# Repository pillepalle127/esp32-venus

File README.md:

# ESP32-S3 statt Venus OS

Ich will die Funktionen von Venus OS, die ich nutze, auf einem ESP32-S3 nachbauen. Eine Portierung geht nicht: Venus OS ist eine Linux-Distribution, und ein kompletter Build braucht private Repos von Victron.

## Ziel

1. Den Pi ersetzen (`raspberrypi2`, 192.168.1.10).
2. Den Netzzähler gleich mit übernehmen (MT681, heute `victron_meter.be` auf Tasm_Kellercenter2). Später ziehen auch Lüfter und BME280 um, dann entfällt der Tasmota ganz.
3. Zum Schluss die zwei ESP32-S3 ersetzen, die heute parallel laufen: die OpenDTU-OnBattery (DTUoB_WP) regelt den WP-HMS, die OpenDTU (HMS Garage) liefert nur Werte. Die Wechselrichter bleiben.

## Anlage laut Venus (02.11.2026)

| Dienst | Instanz | Gerät | Anschluss |
|---|---|---|---|
| `vebus.ttyUSB0` | 288 | MultiPlus-II 48/5000/70-50 | VE.Bus |
| `solarcharger.ttyUSB1` | 293 | BlueSolar MPPT 100/20 48V | USB |
| `solarcharger.ttyUSB2` | 294 | BlueSolar MPPT 100/20 48V | USB |
| `solarcharger.ttyUSB4` | 296 | BlueSolar MPPT 100/20 48V | USB |
| `solarcharger.ttyUSB5` | 291 | SmartSolar MPPT 100/20 48V | USB |
| `solarcharger.ttyUSB6` | 288 | SmartSolar MPPT 100/20 48V | USB |
| `solarcharger.ttyUSB7` | 292 | BlueSolar MPPT 100/20 48V | USB |
| `battery.ttyUSB8` | 291 | SmartShunt IP65 300A | USB |
| `battery.socketcan_can1` | 512 | JK-BMS | CAN |
| `grid.ve_TM974E88` | 40 | Netzzähler MT681 | SML 9600 Baud an Tasm_Kellercenter2. Venus liest per Modbus UDP von 192.168.1.33, `victron_meter.be` gibt den Tasmota als Victron-Zähler VM-3P75CT aus |
| `pvinverter.http_34`, `inverter.http_34` | 34 | Hoymiles HMS-1600 (Garage) und HMS-2000 (WP) | Funk über OpenDTU und OpenDTU-OnBattery, Venus liest per HTTP (`dbus-opendtu_Garage`, `dbus-opendtu_WP`) |
| `pvinverter.mqtt_pv_100` | 100 | Growatt MIC, über `dbus-mqtt-pv` | MQTT |

- Akku: zwei Packs parallel, je 15s1p aus Zellen Eve LF230, jedes Pack mit eigenem JK-BMS der PB-Reihe. Primär: JK-PB2A16S20P V19 (8–16S, 200 A, 2 A aktiver Balancer). Sekundär: JK-PB1A16S15P V15 (8–16S, 150 A, 1 A aktiver Balancer).
- Heizung: Das JK-BMS schaltet seinen Heizausgang selbst. Freigabe bei der PB-Reihe über RS485, Register `0x0114` Bit 0 (`HeatEN`, lesen und schreiben, im selben Register stehen weitere Schalter), dazu Start- und Stopptemperatur. Über CAN gibt es keinen Befehl dafür. Quelle: [jkbms-rs485-addon #177](https://github.com/jean-luc1203/jkbms-rs485-addon/issues/177), an meinen BMS nicht geprüft.
- Unter 0 °C an der Batterie muss der Heizer aktiviert werden. Der Heizer ist noch nicht aktiv, deshalb muss unter 0 °C das Laden abgeschaltet werden.
- Als SoC gilt immer der Wert des SmartShunt (battery 291). Der SoC des JK-BMS driftet viel stärker und hat einen hohen Messfehler.
- Die seriellen Anschlüsse laufen heute über 2 × FT4232 am Pi, alle Kanäle mit Isolatoren.
- Firmware der MPPT v1.74 (`372` = `0x174`), MultiPlus v508 (`1288` = `0x508`).
- `can1`: 500 kbit/s, MCP2515 am Pi.
- Die MPPT laufen nachts aus der Batterie und lassen sich lesen.

## Entscheidungen

- Ein ESP32-S3 für alles.
- Die FT4232 ersetze ich durch einen CH348. Der läuft allerdings nicht an Venus.
- Von OpenDTU-OnBattery nutze ich nur Überwachung und Steuerung des Hoymiles HMS zur Einspeisung. Es ist deshalb keine Basis für dieses Projekt.
- Die Verbindung zu VRM bleibt (Entscheidung vom 18.11.2026). ESP_venus meldet selbst an VRM, so wie der vrmlogger in Venus OS. Was Venus heute sendet: [docs/vrm.md](docs/vrm.md).

## Serielle Anschlüsse

- Der USB-Host des S3 kann nur Full Speed und hat 8 Kanäle, jeder Endpunkt belegt einen. 2 × FT4232 geht deshalb nicht, schon einer braucht 9.
- Der CH348 läuft am S3 mit Full Speed über 4 Bulk-Endpunkte, mit EP0 sind das 5 von 8 Kanälen. Sein Protokoll ist nicht offen. Die Befehle in meinem Treiber stammen aus `ch9344ser_linux` von WCH (GPL-2.0), verglichen mit dem ESPHome-PR #14586.
- Für die beiden RS485 zu den Packs nehme ich einen SC16IS752 (CJMCU-752, SPI, 2 UARTs). Der CH9434 ist schlecht verfügbar.
- Pegel: Die MPPT senden mit 5 V, die Isolatoren bleiben. Der CH348 läuft nur mit 3,3 V, die Isolatoren auf seiner Seite deshalb auch. 5 V vertragen nur RXD0, RXD2, RXD4 und RXD7.

## Belegung (wie verdrahtet, 14.11.2026)

| Funktion | Signal | GPIO | Anschluss |
|---|---|---|---|
| VE.Bus, UART1, 256000 Baud | RX / TX | 4 / 5 | RS485-Modul (MS2548), über ADuM1201 und B0505S isoliert |
| MT681 Haus, UART2, 9600 Baud | RX | 7 | Pfostenstecker MT681: GND, 3V3, Haus, WP |
| MT681 Wärmepumpe, RMT, 9600 Baud | RX | 6 | Pfostenstecker MT681 |
| Kellerlüftung, I²C | SDA / SCL | 16 / 15 | die beiden BME280 (0x76 außen, 0x77), je ein Pfostenstecker: GND, 3V3, SDA, SCL |
| Funk, ein CMT2300A für beide HMS | CSB, SDIO, SCLK, FCSB | 8, 3, 46, 9 | Modul per Pigtail am S3 angelötet, VCC an 3V3 |
| Kellerlüftung | Lüfter | 11 | Relais |
| Reserve | Relais 2 | 12 | Relais |
| JK-BMS, TWAI, 500 kbit/s | TX / RX | 14 / 13 | TJA1050, über ADuM1201 und B0505S isoliert |
| JK-BMS, RS485 je Pack, SC16IS752 per SPI | CS, SI, SO, SCLK | 2, 42, 41, 38 | CJMCU-752 mit Quarz 1,8432 MHz (höchstens 115200 Baud), VCC an 5 V für den AMS1117 auf dem Modul, UART A und B je über ADuM1201, B0505S und RS485-Modul (MS2548) isoliert, nur für die Zellspannungen |
| RGB-LED des Boards | WS2812 | 48 | über die Lötbrücke „RGB“ |
| Reserve | | 1, 10, 17, 18, 21, 39, 40, 47 | |
| Flashen, UART0 beim Start | TX / RX | 43 / 44 | COM-Buchse auf dem Board |
| CH348, USB-Host | D− / D+ | 19 / 20 | native USB-Buchse, 5 V über die Brücke `USB-OTG` |
| nicht beschalten | Strapping | 0, 45 | |
| belegt | Octal-PSRAM | 33–37 | |

| CH348 | Gerät |
|---|---|
| Port 0–5 | die 6 MPPT, über die vorhandenen Isolatoren |
| Port 6 | SmartShunt, über den vorhandenen Isolator |
| Port 7 | frei, für einen weiteren MPPT |

- Zum JK-BMS laufen zwei Wege. **CAN steuert:** Ladegrenzen, Alarme, SoC, beide Packs zusammengefasst, ohne CAN keine DVCC-Vorgaben. **RS485 zeigt an:** einzelne Zellspannungen, die Regelung hängt nicht daran.
- Der Netzzähler bleibt am eigenen UART, er liefert das Regelsignal fürs ESS. Der zweite MT681 läuft per RMT als Empfangs-UART. Die Zellspannungen beider Packs laufen über den SC16IS752, UART0 bleibt Konsole.
- Welcher MPPT an welchem Port hängt, spielt keine Rolle: Die Firmware erkennt jedes Gerät an seiner Seriennummer und gibt ihm die Instanz von heute.
- GPIO 3 und 46 sind Strapping-Pins und tragen nur Eingänge des CMT2300A. GPIO 46 hält der interne Pull-down beim Reset low. GPIO 3 wirkt nur mit gesetzter eFuse `STRAP_JTAG_SEL`.
- Ein Ausfall des WLAN trifft nur ioBroker und VRM, nicht die Regelung.

## Trennung und Transceiver

Lochraster-Plan: [docs/layout_lochraster.drawio](docs/layout_lochraster.drawio), Belegung der Stiftleisten: [docs/layout_lochraster.md](docs/layout_lochraster.md).

Eigene Platine, Plan mit Steckverbindungen und Blockdiagramm: [docs/platine.md](docs/platine.md).

- Die BMS schalten im Minus-Zweig. Hängt der S3 ohne Trennung an zwei Stellen, überbrückt seine Masse einen offenen BMS-Schalter. Ich trenne deshalb VE.Bus, CAN und RS485, jeweils an TX und RX, mit ADuM1201 und einem eigenen B0505S-1W je Busseite. GND bleibt am Bus.
- Das ist eine Funktionstrennung gegen rund 60 V, kein Schutz vor Netzspannung.
- Der B0505S-1WR3 ist ungeregelt und braucht mindestens 20 mA Last. Der TJA1050 sendet nur bei 4,75–5,25 V. Ist die Spannung bei wenig Last zu hoch, hilft ein Lastwiderstand (250 Ω = 10 % Last).
- Der ADuM1201AR reicht für CAN: höchstens rund 0,8 µs Laufzeit, der S3 tastet nach 1,6 µs ab.
- **RS485-Module (VE.Bus und Packs):** Auf den Modulen im Lochraster sitzt ein MS2548 von Ruimeng, kein MAX13487. Die eigene Platine nimmt das kleine Modul mit MAX13487 („RS485 V2.05“), siehe [docs/platine.md](docs/platine.md#busseiten).
- Der MS2548 schaltet die Richtung selbst: D low treibt low, D high treibt kurz high und gibt frei. Den Ruhezustand halten Pull-up an A und Pull-down an B.
- An VE.Bus müssen Pull-up und Pull-down runter. Mit ihnen lag der Bus bei 4,5–10 kΩ, der MultiPlus ging beim Einstecken auf Störung (17.11.2026). Ohne sie empfängt und sendet der MS2548 an VE.Bus: Sync, 0 Prüfsummenfehler, jeder ESS-Befehl quittiert.
- **TJA1050 (CAN):** Der TWAI des S3 braucht nur den Transceiver, keinen MCP2515.
- Eigene Platine: CAN an Stecker X5 (1 GND, 2 CANH, 3 CANL). Layout: [docs/platine.md](docs/platine.md#layout).

## Relaistreiber

Zwei 5-V-Relais von Finder, je Low-Side über AO3402 (100 Ω Gate, 10 kΩ Pull-down, Freilaufdiode). GPIO high schaltet ein. Der AO3402 hat laut Datenblatt höchstens 85 mΩ bei 2,5 V Gate-Spannung.

| Relais | GPIO | In der Firmware |
|---|---|---|
| Lüfter, Kellerlüftung | 11 | `FAN_RELAY` |
| Relais 2, Reserve | 12 | `RELAY2` |

- Eigene Platine: Stecker X6 (Lüfter) und X7 (Relais 2), je 1 +5V, 2 Schalter. Layout: [docs/platine.md](docs/platine.md#layout).
- Firmware: Nach dem Start bleiben GPIO 11 und 12 Eingang, erst ein Knopf auf der Seite macht sie zum Ausgang.

## DVCC

DVCC ist aktiv, der S3 muss es also ersetzen: die Ladegrenzen vom JK-BMS lesen und an alle sechs MPPT und den MultiPlus weitergeben.

Laut MPPT-HEX-Protokoll von Victron:
- **External Control (ESS, DVCC):** `0x200E` = `b0000101`, Vorgaben in `0x2001` und `0x2015`. Ohne Daten fällt der MPPT nach 1 Minute auf Stand-alone zurück.
- **BMS-Modus:** `0x200E` = `b0001001`. Der MPPT setzt dabei `BMS present` (`0xEDE8`) und speichert das im Flash. Danach läuft er nicht mehr alleine: Ohne Daten hört er auf zu laden und zeigt Fehler #67. Morgens lädt er 45 s in Float, damit das BMS starten kann.
- Ab Firmware 1.53 unterdrücken HEX-Anfragen den Text-Modus nicht mehr. Textblöcke kommen im Abstand von 1 s.

Auf allen sechs MPPT steht `NetworkMode` = 13 (Networked, External Control, BMS) und `BmsPresent` = 1. Ohne Vorgaben vom S3 stoppen sie mit Fehler #67.

Am 04.11.2026 gesehen ([Mitschnitt](docs/venus_mppt_0v_2026-11-04.txt)): Ohne Netzzähler und mit `RunWithoutGridMeter` = 0 meldet der MP2 `/Hub/ChargeVoltage` 0.0. DVCC gibt den MPPT dann 0 V, und sie laden nicht. `Mode` = 3 allein half nicht, `RunWithoutGridMeter` = 1 schon. Der S3 schickt den MPPT nie 0 V.

## Software

- Firmware in `firmware/`: PlatformIO mit Arduino 3.3.12 auf ESP-IDF 5.5.5 (`pioarduino`). Der USB-Treiber braucht ein aktuelles IDF, und beide Bibliotheken bauen auf Arduino auf.
- VE.Bus: `ve.bus-library` (MIT). Läuft am S3 mit dem MultiPlus: Mithören und ESS-Sollwert senden (17.11.2026).
- Hoymiles: `lib/Hoymiles` aus OpenDTU, laut Dateiköpfen GPL-2.0-or-later. Herkunft der fremden Bibliotheken: `firmware/lib/README.md`. Der CH348-Treiber liegt in `firmware/lib/ch348/`.
- Neu: VE.Direct, SML, JK-BMS über CAN, DVCC, ESS-Regelung, Stützung der Wärmepumpe, MQTT, Webseite.
- Aus `victron_meter.be` übernehmen: Der MT681 hat keinen Einspeisezähler (2.8.0), die Einspeisung wird integriert und alle 10 min gesichert. Der Zähler ist einphasig auf L1 abgebildet.

ioBroker soll nichts merken: gleiche Adresse 192.168.1.10:1883, Benutzer `remoteconsole`, Portal-ID `b827ebc35935`, gleiche Themen, Werte als `{"value": x}`. Dazu braucht der S3 einen eigenen MQTT-Broker.
- Lesen: 38 N-Themen, die Bereiche stehen in `~/projects/Kellerlüftung/mqtt1_abo.txt`. Noch nicht umgesetzt: Die Firmware veröffentlicht bisher nichts.
- Schreiben: `AcPowerSetPoint`, `vebus.288.Mode`, `BatteryLife/State`.
- `mqtt_pv_100` ist der Growatt MIC. Venus bindet ihn mit [venus-os_dbus-mqtt-pv](https://github.com/mr-manuel/venus-os_dbus-mqtt-pv) ein: höchstens 1600 W, AC-Eingang 1, Topic `Growatt_fake/power` am Broker 192.168.1.4. Kommt 60 s nichts, beendet sich der Treiber. Das Topic schreibt das ioBroker-Skript `script.js.common.Photovoltaik`. Das muss weiter ankommen.

## Speicher (interner RAM)

Knapp ist der interne RAM: Dort liegen die Stapel der Tasks, die die Bibliotheken selbst anlegen, und mbedtls. Werte von ESP_venus, gemessen am 19.11.2026 (Webseite: `/tasks.txt`, Reiter VRM):

| Stand | intern frei | Tiefstwert |
|---|---|---|
| Firmware vom 17.11. ohne VRM, nach 3,7 h | 102 kB | 98 kB |
| VRM, erste Fassung | 43 kB | 29 kB |
| VRM, mbedtls und eigene Stapel im PSRAM, Stapel und Puffer verkleinert | 73 kB | 63 kB |

VRM kostet damit rund 28 kB intern. Davon:
- Quelle (MQTT zum Pi, nur im Übergang): Stapel 5 kB (3,1 kB benutzt), Puffer 2 × 1 kB.
- Brücke (MQTT zu VRM): Stapel 5,5 kB (2,8 kB benutzt, TLS-Aufbau eingeschlossen), Puffer 2 × 1 kB.

Änderungen:
- **mbedtls:** Arduino stellt es auf internen RAM (`CONFIG_MBEDTLS_INTERNAL_MEM_ALLOC`). Zwei TLS-Verbindungen scheiterten daran mit `-0x7F00` (Speicher). Die Firmware setzt beim Start `mbedtls_platform_set_calloc_free` auf PSRAM.
- **Eigene Tasks `vrm` und `vrm_live`:** Stapel im PSRAM (`xTaskCreatePinnedToCoreWithCaps`). Das geht nur für Tasks, die nicht in den Flash schreiben.
- **Stapel von esp-mqtt:** liegen immer intern, deshalb auf das Gemessene verkleinert.

Nicht gemacht: `heap_caps_malloc_extmem_enable`. Das träfe auch VE.Bus, USB und CAN.

## VE.Bus laut Quellen (nicht von mir gemessen)

- 256000 Baud, 8N1. Sync-Frame alle 20 ms.
- `ve.bus-library` sendet nur 8,0–9,5 ms nach dem Sync und lässt sonst einen Sync aus.
- Der ESS-Sollwert muss spätestens alle 60 s kommen, sonst geht der MultiPlus in Passthrough.
- Vor OTA oder Neustart den Bus stumm schalten (`setTxEnabled(false)`).
- esp32ess läuft auf einem MultiPlus-II 48/5000 mit Firmware v502 (meiner: v508) und kann nur ein Gerät (einphasig). Es meldet 1–2 % fehlgeschlagene Befehle, die wiederholt werden.
- Der Bus muss hochohmig bleiben, über 100 kΩ, sonst schaltet sich das Victron-Gerät ab (bei mir am 17.11.2026).
- USB des ESP32 und MultiPlus nie gleichzeitig anschließen (README von PepeTheFroggie).

## Stand

- **CH348 (03.11.2026):** am S3 erkannt, Schleifentest über alle 8 Ports 92 min ohne Fehler, 55,2 MB.
- **VE.Bus-Timing (03.11.2026):** Ein zweiter S3 spielt den MultiPlus. 9000 von 9000 Antworten, Beginn 8,95–10,53 ms nach dem Sync.
- **Testfirmware (Env `s3`, 14.11.2026):** Webseite unter `http://esp32-venus.local/`. Gesendet wird nur auf Knopfdruck (RS485-Test, CAN-Selbsttest) und im Reiter „ESS MultiPlus“ mit „Senden ein“. Auf CAN quittiert der S3 nur. Die Seite hat keine Anmeldung. Die alte Firmware mit CH348-Schleifentest baut als Env `s3_timing`.
- **Am Tisch geprüft (14.11.2026):** beide BME280, beide MT681 am echten Zähler (RMT ohne Rahmenfehler), CAN-Kette per Selbsttest, CH348 mit einem MPPT, Isolation, TX-Pegel bei Reset.
- **An der Anlage (17.11.2026):** RS485 über Kreuz in allen Richtungen, VE.Bus am MultiPlus (hören und senden), CAN am JK-BMS, erster Test der ESS-Regelung mit Nulleinspeisung. Ergebnisse unter C1 im [Testplan](docs/testplan.md).
- **Bekannt:** Nach einem Neustart des S3 meldet sich der CH348 nur, wenn er selbst kurz ohne Strom war.

## Kabelwege und Platz des S3

| Verbindung | Art | Länge |
|---|---|---|
| VE.Bus | RS485, RJ45-Kabel direkt vom S3 zum MultiPlus | unkritisch |
| JK-BMS | CAN, differentiell | unkritisch |
| CH348 | USB, 5 V und Daten | freifliegend am USB-Kabel, bis etwa 3 m |
| VE.Direct | 19200 Baud über die Isolatoren | wie heute am FT4232, wenn der CH348 dort sitzt |
| MT681 | 9600 Baud, 3,3 V | 2 m sind in Ordnung |
| BME280 | I²C | empfindlichste Leitung, nicht länger als heute am Tasmota |
| Funk | SPI, direkt am S3 angelötet | der Platz des S3 ist auch der Platz des Funks |

Die Längen sind Erfahrungswerte, nicht gemessen. Der S3 gehört deshalb eher zu BME280, Zählern und DTUs als zum MultiPlus.

## JK-BMS auf CAN (Mitschnitt 03.11.2026)

Rohdaten: [docs/venus_can_seriennummern_2026-11-03.txt](docs/venus_can_seriennummern_2026-11-03.txt). 21 IDs, zusammen rund 27 Telegramme pro Sekunde. Gelesen nach dem üblichen Victron-Format, an der Anzeige von Venus nicht geprüft.

| ID | Inhalt | Wert im Mitschnitt |
|---|---|---|
| `351` | Ladespannung, Ladestrom, Entladestrom, Entladespannung | 51,8 V, 161,5 A, 289,7 A, 40,5 V |
| `355` | SoC, SoH, SoC fein | 26 %, 100 %, 25,60 % |
| `356` | Spannung, Strom, Temperatur | 48,60 V, −10,7 A, 15,9 °C |
| `35A` | Warnungen und Alarme | `A8A80200A8A80202` |
| `35E`, `370` | Name | `JK-BMS` |
| `372` | Module online | 2 |
| `373` | Zelle min, max, Temperatur min, max | 3233 mV, 3245 mV, 14 °C, 17 °C |
| `374`–`377` | Wo min und max liegen | `01::02`, `00::05`, `00::02`, `01::03` |
| `378` | Energie geladen, entladen | 34432, 31595, vermutlich je 100 Wh |
| `379` | Kapazität | 440 Ah |
| `380`, `381` | Seriennummer | `506036N49005514` |
| `305`, `307` | 1-mal pro Sekunde, `307` endet auf `VIC` | von Venus |

- Die wirksame Ladespannung ist heute 51,8 V vom BMS, unter der Grenze von 52,0 V aus Venus. Beim Ladestrom gilt die Grenze aus Venus: 120 A statt 161,5 A vom BMS.
- `305` und `307` sind das Lebenszeichen von Venus ans BMS. Ohne sie sendete das BMS am 17.11.2026 weiter. Meldet es auf Dauer etwas, sendet der S3 sie.
- Einzelne Zellspannungen stehen nicht auf dem CAN-Bus, nur Minimum und Maximum.

## Geräte an VE.Direct

Die Firmware erkennt die Geräte an der Seriennummer (`firmware/src/devices.h`).

| Seriennummer | Gerät | Instanz | heute an |
|---|---|---|---|
| `HQ2440T6X3F` | SmartSolar 100/20 | 288 | `ttyUSB6` |
| `HQ24444FA7P` | SmartSolar 100/20 | 291 | `ttyUSB5` |
| `HQ2444X92KD` | BlueSolar 100/20 | 292 | `ttyUSB7` |
| `HQ250332J3K` | BlueSolar 100/20 | 293 | `ttyUSB1` |
| `HQ2503KHTNV` | BlueSolar 100/20 | 294 | `ttyUSB2` |
| `HQ2503PZF6F` | BlueSolar 100/20 | 296 | `ttyUSB4` |
| `HQ2512RP9C2` | SmartShunt 300 A | 291 | `ttyUSB8` |

## Offen

- Die DVCC- und ESS-Einstellungen, die der S3 übernehmen muss.
- Einzelzellen: DTUoB_WP liest per RS485 nur ein Pack (Adresse 1). Laut esphome-jk-bms ist je Modbus-Bus nur ein Master erlaubt, ein BMS mit Adresse 0 ist selbst Master. Deshalb bekommt jedes Pack einen eigenen RS485.
- Baudrate am RS485 des JK-BMS.
- MS2548 an VE.Bus über Stunden: Anteil quittierter Befehle, Signal an A–B mit dem Oszilloskop.
- Vorzeichen der AC-out-Leistung des MultiPlus (RAM 16).
- Versorgung über die COM-Buchse geht nicht mehr, vermutlich ist dort die Diode defekt.
- GND am CAN- und RS485-Port des JK-BMS gegen B− messen, dazu VE.Bus Pin 3 gegen DC− des MP2. Ist ein Port schon getrennt, entfällt dort die Trennung.

## Quellen

- [Venus OS Build-Repo](https://github.com/victronenergy/venus)
- [mkrasselt1/ve.bus-library](https://github.com/mkrasselt1/ve.bus-library)
- [pv-baxi/esp32ess, Doku](https://github.com/pv-baxi/esp32ess/blob/main/docs/README.md)
- [PepeTheFroggie/Victron-VE.Bus---esp32](https://github.com/PepeTheFroggie/Victron-VE.Bus---esp32)
- [Victron: ESS mode 2 and 3](https://www.victronenergy.com/live/ess:ess_mode_2_and_3?do=export_pdf)
- [Victron: VE.Direct-Protokoll](https://www.victronenergy.com/upload/documents/VE.Direct-Protocol-3.34.pdf)
- [Victron: VE.Direct FAQ](https://www.victronenergy.com/live/vedirect_protocol:faq?do=export_pdf)
- [MPPT HEX-Protokoll](https://www.mikrocontroller.net/attachment/522263/MPPT-HEX-Protocol.pdf)
- [CH348 Datenblatt](https://files.waveshare.com/wiki/USB-TO-8CH-TTL/CH348DS1.PDF)
- [CH348 Linux-Patch v8](https://ratatoskr.run/lkml/2025/02/2911285/t)
- [WCH: ch9344ser_linux](https://github.com/WCHSoftGroup/ch9344ser_linux)
- [ESPHome-PR #14586: CH9344 und CH348](https://github.com/esphome/esphome/pull/14586)
- [Waveshare: USB TO 8CH TTL](https://www.waveshare.com/wiki/USB_TO_8CH_TTL)
- [esphome-jk-bms #706: Master und Slave](https://github.com/syssi/esphome-jk-bms/issues/706)
- [Multiple JK BMS by Modbus RS485](https://github.com/phinix-org/Multiple-JK-BMS-by-Modbus-RS485)
- [SC16IS752 Datenblatt](https://www.nxp.com/docs/en/data-sheet/SC16IS752_SC16IS762.pdf)
- [nopnop2002/esp-idf-sc16is750](https://github.com/nopnop2002/esp-idf-sc16is750)
- [dbus-systemcalc-py](https://github.com/victronenergy/dbus-systemcalc-py)
- [dbus-flashmq](https://github.com/victronenergy/dbus-flashmq/blob/master/README.md)
- [mlesniew/PicoMQTT](https://github.com/mlesniew/PicoMQTT)
- [ESP-IDF: USB Host, Hinweise zum DWC_OTG](https://docs.espressif.com/projects/esp-idf/en/v5.5.4/esp32s3/api-reference/peripherals/usb_host/usb_host_notes_dwc_otg.html)
- [ESP-IDF: USB Host](https://docs.espressif.com/projects/esp-idf/en/stable/esp32s3/api-reference/peripherals/usb_host.html)
- [ESPHome: USB Host](https://esphome.io/components/usb_host/)
- [tbnobody/OpenDTU](https://github.com/tbnobody/OpenDTU)
- [hoylabs/OpenDTU-OnBattery](https://github.com/hoylabs/OpenDTU-OnBattery)
- [nRF24/RF24](https://github.com/nRF24/RF24)
- [pioarduino/platform-espressif32](https://github.com/pioarduino/platform-espressif32)
- [henne49/dbus-opendtu](https://github.com/henne49/dbus-opendtu)
- [mr-manuel/venus-os_dbus-mqtt-pv](https://github.com/mr-manuel/venus-os_dbus-mqtt-pv)
- [syssi/esphome-jk-bms](https://github.com/syssi/esphome-jk-bms)
- [ArminJo/JK-BMSToPylontechCAN](https://github.com/ArminJo/JK-BMSToPylontechCAN)
- [JK-BMS CAN-Protokoll V1.02](http://www.jk-bms.com/Upload/2022-05-19/1619062896.pdf)
- [ESP-IDF: TWAI](https://docs.espressif.com/projects/esp-idf/en/stable/esp32s3/api-reference/peripherals/twai.html)
- [TJA1050 Datenblatt (NXP)](https://www.nxp.com/docs/en/data-sheet/TJA1050.pdf)
- [ESP32-S3 Datenblatt](https://documentation.espressif.com/esp32-s3_datasheet_en.pdf)
- [MS2548 Datenblatt (Ruimeng, chinesisch)](https://www.ftelectronic.com/Public/Upload/news/20231228/658d3c0d6c997.pdf)
- [MS2548 bei LCSC](https://www.lcsc.com/product-detail/C42415856.html)
- [ADuM1200/ADuM1201 Datenblatt](https://www.analog.com/media/en/technical-documentation/data-sheets/adum1200_1201.pdf)
- [AO3402 Datenblatt (AOS)](https://www.aosmd.com/sites/default/files/res/datasheets/AO3402.pdf)
- [B0505S Datenblatt (Mornsun, Serie B_S-1WR3)](https://www.mornsun-power.com/public/uploads/pdf/B_S-1WR3.pdf)

## Lizenz

GPL-2.0-or-later, siehe [LICENSE](LICENSE). Die fremden Bibliotheken in `firmware/lib/` stehen unter ihren eigenen Lizenzen, siehe [firmware/lib/README.md](firmware/lib/README.md).

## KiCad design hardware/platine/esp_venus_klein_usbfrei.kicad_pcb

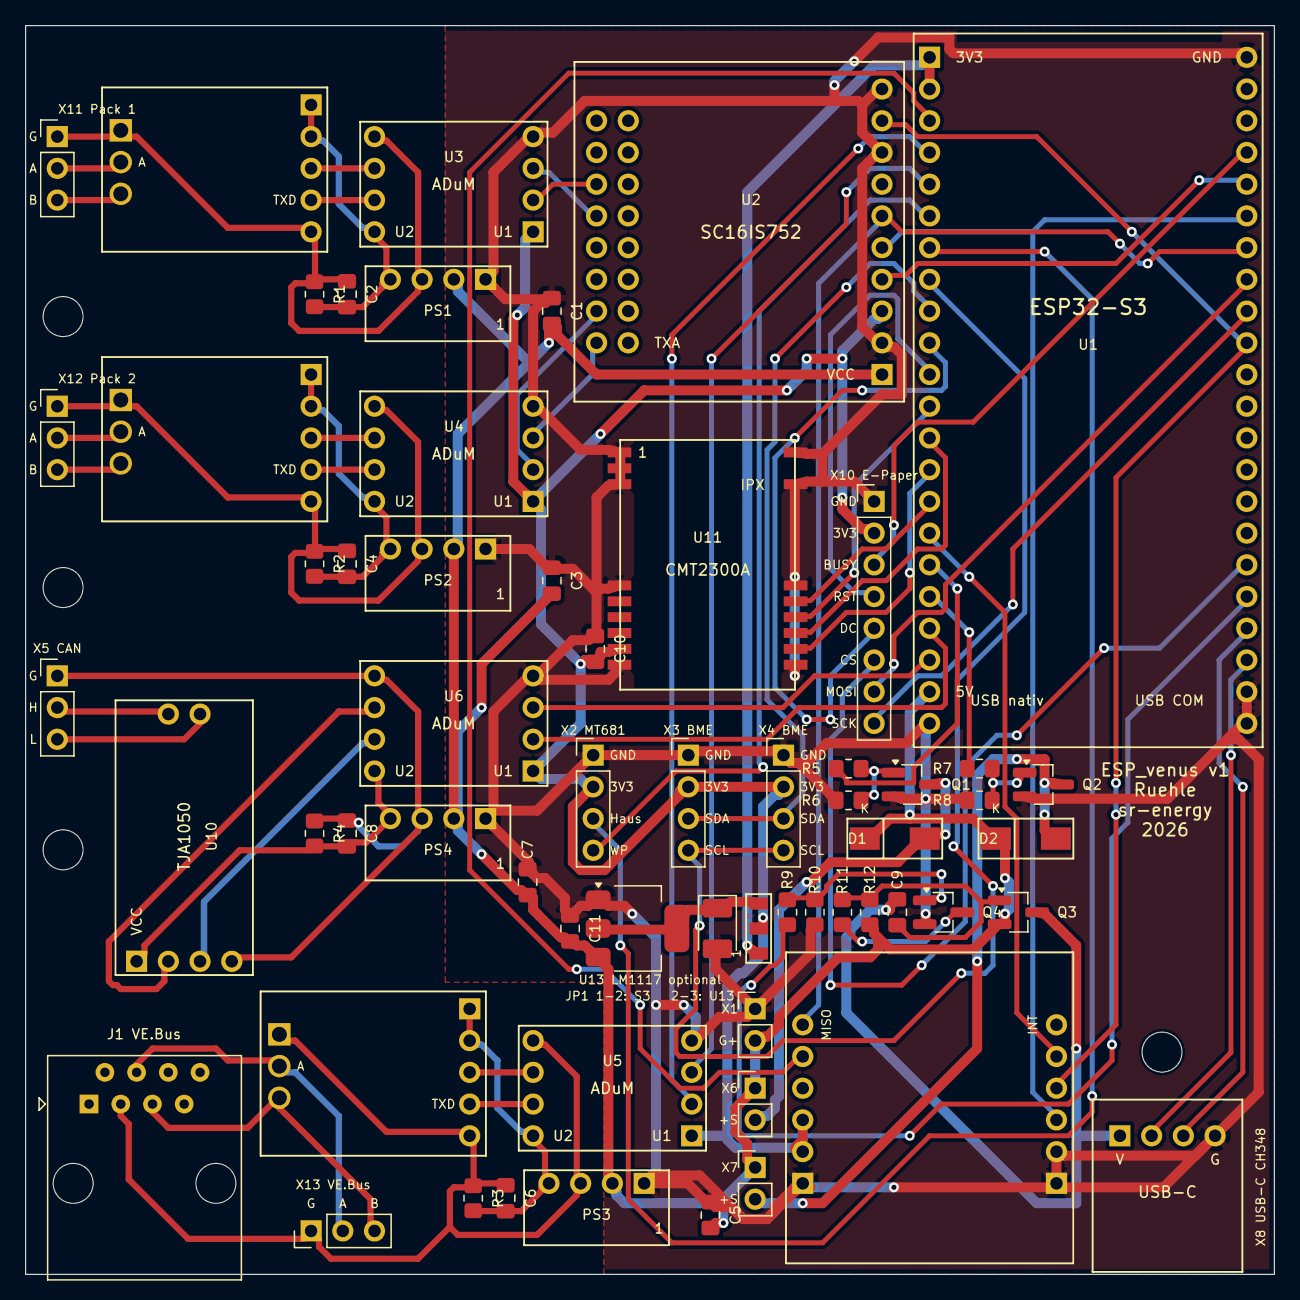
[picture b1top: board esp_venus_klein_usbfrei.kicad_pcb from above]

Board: 2 copper layers, 100.0 x 100.0 mm, 65 parts (0 on the bottom side), 70 nets.

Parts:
C1, C3, C5, C7: 4,7u Cin; C_0805_2012Metric_Pad1.18x1.45mm_HandSolder
C2, C4, C6, C8: 10u Cout; C_0805_2012Metric_Pad1.18x1.45mm_HandSolder
C9: 100n; C_0805_2012Metric_Pad1.18x1.45mm_HandSolder
C10: 100n CMT; C_0805_2012Metric_Pad1.18x1.45mm_HandSolder
C11: 10u Vin; C_0805_2012Metric_Pad1.18x1.45mm_HandSolder
C12: 10u Tantal; CP_EIA-3528-21_Kemet-B_Pad1.50x2.35mm_HandSolder
D1, D2: S1M oder 1N4148W; D_SMA_SOD-123_kombiniert
H1, H2, H3, H4: M3; MountingHole_3.2mm_M3
J1: RJ45 VE.Bus; RJ45_Amphenol_54602-x08_Horizontal
JP1: 3V3: 1-2 S3, 2-3 U13; Loetbruecke_3
PS1: B0505S Pack 1; B0505S-1WR3
PS2: B0505S Pack 2; B0505S-1WR3
PS3: B0505S VE.Bus; B0505S-1WR3
PS4: B0505S CAN; B0505S-1WR3
Q1, Q2, Q4: AO3402; SOT-23_Handsoldering
Q3: AO3401A; SOT-23_Handsoldering
R1, R2, R3, R4: Last, unbestueckt; R_0805_2012Metric_Pad1.20x1.40mm_HandSolder
R5, R7, R9: 100R; R_0805_2012Metric_Pad1.20x1.40mm_HandSolder
R6, R8, R10, R11: 10k; R_0805_2012Metric_Pad1.20x1.40mm_HandSolder
R12: 100k; R_0805_2012Metric_Pad1.20x1.40mm_HandSolder
U1: ESP32-S3 N16R8; ESP32-S3_N16R8_2xUSB-C
U2: SC16IS752; CJMCU-752
U3: ADuM1201 Pack 1; ADuM1201_Modul
U4: ADuM1201 Pack 2; ADuM1201_Modul
U5: ADuM1201 VE.Bus; ADuM1201_Modul
U6: ADuM1201 CAN; ADuM1201_Modul
U7: RS485 Pack 1; RS485_MAX13487_klein
U8: RS485 Pack 2; RS485_MAX13487_klein
U9: RS485 VE.Bus; RS485_MAX13487_klein
U10: TJA1050; TJA1050_Modul
U11: CMT2300A; CMT2300A_10298-V1.0
U12: W5500; W5500_USR-ES1
U13: LM1117-3.3; SOT-223-3_TabPin2
X1: X1; PinHeader_1x02_P2.54mm_Vertical
X2: MT681; PinHeader_1x04_P2.54mm_Vertical
X3: BME280 1; PinHeader_1x04_P2.54mm_Vertical
X4: BME280 2; PinHeader_1x04_P2.54mm_Vertical
X5: CAN; PinHeader_1x03_P2.54mm_Vertical
X6: X6; PinHeader_1x02_P2.54mm_Vertical
X7: X7; PinHeader_1x02_P2.54mm_Vertical
X8: USB-C CH348; USB-C_Modul_12x13.8
X10: E-Paper; PinHeader_1x08_P2.54mm_Vertical
X11: Pack 1 A B GND; PinHeader_1x03_P2.54mm_Vertical
X12: Pack 2 A B GND; PinHeader_1x03_P2.54mm_Vertical
X13: VE.Bus A B GND; PinHeader_1x03_P2.54mm_Vertical

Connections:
3V3_ESP: JP1.1, U1.3V3
3V3_LDO: C12.1, JP1.3, U13.2
+3V3: C10.1, JP1.2, U2.RESET, U3.U1, U4.U1, U5.U1, U6.U1, U11.8, U12.3V3, X2.2, X3.2, X4.2, X10.2
+5V: C1.1, C3.1, C5.1, C7.1, C11.1, D1.1, D2.1, PS1.2, PS2.2, PS3.2, PS4.2, Q3.2, R12.1, U1.5V, U2.VCC, U13.3, X1.2, X6.1, X7.1
CAN_5V: C8.1, PS4.4, R4.1, U6.U2, U10.VCC
CAN_GND: C8.2, PS4.3, R4.2, U6.G2, U10.GND, X5.1
CAN_H: U10.CANH, X5.2
CAN_L: U10.CANL, X5.3
CAN_RXD: U6.A1, U10.RX
CAN_TXD: U6.B0, U10.TX
CMT_CSB: U1.IO8, U11.13
CMT_FCSB: U1.IO9, U11.14
CMT_SCLK: U1.IO46, U11.11
CMT_SDIO: U1.IO3, U11.12
EPD_BUSY: U1.IO1, X10.3
EPD_CS: U1.IO47, X10.6
EPD_DC: U1.IO17, X10.5
EPD_MOSI: U1.IO40, X10.7
EPD_RST: U1.IO18, X10.4
EPD_SCK: U1.IO39, X10.8
ETH_CS: U1.IO10, U12.CS
ETH_RST: U1.RST, U12.RST
FAN: R5.1, U1.IO11
FAN_G: Q1.1, R5.2, R6.2
FAN_SW: D1.2, Q1.3, X6.2
GND: C1.2, C3.2, C5.2, C7.2, C10.2, C11.2, C12.2, PS1.1, PS2.1, PS3.1, PS4.1, Q1.2, Q2.2, Q4.2, R6.1, R8.1, R10.1, U1.GND, U2.GND, U2.SPI, U2.VSS, U3.G1, U4.G1, U5.G1, U6.G1, U11.1, U11.2, U11.3, U11.4, U11.9, U11.10, U11.15, U11.16, U11.18, U12.GND, U13.1, X1.1, X2.1, X3.1, X4.1, X8.4, X10.1
I2C_SCL: U1.IO15, X3.4, X4.4
I2C_SDA: U1.IO16, X3.3, X4.3
MT_HAUS: U1.IO7, X2.3
MT_WP: U1.IO6, X2.4
P1_5V: C2.1, PS1.4, R1.1, U3.U2, U7.EN, U7.VCC
P1_A: U7.A, X11.2
P1_B: U7.B, X11.3
P1_D: U3.B0, U7.RXD
P1_GND: C2.2, PS1.3, R1.2, U3.G2, U7.GND, X11.1
P1_R: U3.A1, U7.TXD
P2_5V: C4.1, PS2.4, R2.1, U4.U2, U8.EN, U8.VCC
P2_A: U8.A, X12.2
P2_B: U8.B, X12.3
P2_D: U4.B0, U8.RXD
P2_GND: C4.2, PS2.3, R2.2, U4.G2, U8.GND, X12.1
P2_R: U4.A1, U8.TXD
REL2: R7.1, U1.IO12
REL2_G: Q2.1, R7.2, R8.2
REL2_SW: D2.2, Q2.3, X7.2
SC_CS: U1.IO2, U2.CS
SC_SCLK: U1.IO38, U2.SCLK, U12.SCK
SC_SI: U1.IO42, U2.SI, U12.MOSI
SC_SO: U1.IO41, U2.SO, U12.MISO
TWAI_RX: U1.IO13, U6.A0
TWAI_TX: U1.IO14, U6.B1
UARTA_RX: U2.RXA, U4.A0
UARTA_TX: U2.TXA, U4.B1
UARTB_RX: U2.RXB, U3.A0
UARTB_TX: U2.TXB, U3.B1
USB_DM: U1.IO19, X8.2
USB_DP: U1.IO20, X8.3
USB_EN: R9.1, U1.IO21
USB_EN_G: Q4.1, R9.2, R10.2
USB_PG: C9.1, Q3.1, R11.2, R12.2
USB_SW: Q4.3, R11.1
USB_VBUS: C9.2, Q3.3, X8.1
VEBUS_RX: U1.IO4, U5.A0
VEBUS_TX: U1.IO5, U5.B1
VE_5V: C6.1, PS3.4, R3.1, U5.U2, U9.EN, U9.VCC
VE_A: J1.4, U9.A, X13.2
VE_B: J1.5, U9.B, X13.3
VE_D: U5.B0, U9.RXD
VE_GND: C6.2, J1.3, PS3.3, R3.2, U5.G2, U9.GND, X13.1
VE_R: U5.A1, U9.TXD

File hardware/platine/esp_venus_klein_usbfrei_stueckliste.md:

# Stückliste esp_venus_klein_usbfrei.kicad_pcb

Erzeugt aus der Platinendatei. Gleiche Teile mit gleichem Wert sind zusammengefasst.

| Anzahl | Art | Teil | Wert | Bezeichner | Hinweis |
|---|---|---|---|---|---|
| 4 | Modul | ADuM1201-Modul, 15 × 10 mm |  | U3 (ADuM1201 Pack 1), U4 (ADuM1201 Pack 2), U5 (ADuM1201 VE.Bus), U6 (ADuM1201 CAN) | Stiftleisten 2 × 4 |
| 1 | Modul | CMT2300A, Modul 10298-V1.0 |  | U11 | SMD aufgelötet, Antenne an der IPX-Buchse |
| 1 | Modul | ESP32-S3-Board N16R8 mit 2 × USB-C |  | U1 (ESP32-S3 N16R8) | Stiftleisten 2 × 22 direkt eingelötet |
| 3 | Modul | RS485-Modul MAX13487 „RS485 V2.05“, etwa 18 × 12,6 mm |  | U7 (RS485 Pack 1), U8 (RS485 Pack 2), U9 (RS485 VE.Bus) | Stiftleisten 1 × 5 und 1 × 3 |
| 1 | Modul | SC16IS752 (CJMCU-752), Quarz 1,8432 MHz |  | U2 (SC16IS752) | Stiftleisten 1 × 10 und 2 × 8 |
| 1 | Modul | TJA1050-Modul, 22 × 11 mm |  | U10 (TJA1050) | Stiftleiste 1 × 4 und 2 Stifte |
| 1 | Modul | USB-C-Modul 12 × 13,8 mm (V, D−, D+, G) |  | X8 (USB-C CH348) | Stiftleiste 1 × 4 |
| 1 | Modul | W5500-Modul USR-ES1 (W5500 Lite) |  | U12 (W5500) | Stiftleisten 2 × 6 |
| 4 | Bauteil | DC/DC-Wandler B0505S-1WR3, SIP-4 |  | PS1 (B0505S Pack 1), PS2 (B0505S Pack 2), PS3 (B0505S VE.Bus), PS4 (B0505S CAN) | THT |
| 2 | Bauteil | Diode S1M (SMA) oder 1N4148W (SOD-123) | S1M oder 1N4148W | D1, D2 | SMD |
| 1 | Bauteil | Keramik-C 0805 | 100n | C9 | SMD |
| 1 | Bauteil | Keramik-C 0805 | 100n CMT | C10 | SMD |
| 4 | Bauteil | Keramik-C 0805 | 10u Cout | C2, C4, C6, C8 | SMD |
| 1 | Bauteil | Keramik-C 0805 | 10u Vin | C11 | SMD |
| 4 | Bauteil | Keramik-C 0805 | 4,7u Cin | C1, C3, C5, C7 | SMD |
| 1 | Bauteil | MOSFET, SOT-23 | AO3401A | Q3 | SMD |
| 3 | Bauteil | MOSFET, SOT-23 | AO3402 | Q1, Q2, Q4 | SMD |
| 1 | Bauteil | Spannungsregler LM1117-3.3, SOT-223 | LM1117-3.3 | U13 | SMD, optional, nur mit JP1 auf 2-3 |
| 1 | Bauteil | Tantal-C, Bauform B (3528) | 10u Tantal | C12 | SMD, optional, nur mit U13 |
| 3 | Bauteil | Widerstand 0805 | 100R | R5, R7, R9 | SMD |
| 1 | Bauteil | Widerstand 0805 | 100k | R12 | SMD |
| 4 | Bauteil | Widerstand 0805 | 10k | R6, R8, R10, R11 | SMD |
| 4 | Bauteil | Widerstand 0805 | unbestückt, bei Bedarf 250 Ω | R1, R2, R3, R4 | SMD |
| 1 | Stecker | RJ45-Buchse liegend, Bauform Amphenol 54602 | RJ45 VE.Bus | J1 | THT |
| 3 | Stecker | Stiftleiste 1 × 2, Raster 2,54 mm |  | X1, X6, X7 | THT |
| 4 | Stecker | Stiftleiste 1 × 3, Raster 2,54 mm |  | X5, X11, X12, X13 | THT |
| 3 | Stecker | Stiftleiste 1 × 4, Raster 2,54 mm |  | X2, X3, X4 | THT |
| 1 | Stecker | Stiftleiste 1 × 8, Raster 2,54 mm |  | X10 | THT |
| 1 | Lötbrücke | Lötbrücke, 3 Pads | 3V3: 1-2 S3, 2-3 U13 | JP1 | kein Bauteil, mit Zinn schließen |

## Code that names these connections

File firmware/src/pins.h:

// Pinbelegung, siehe README und docs/layout_lochraster.drawio. Verdrahtet und benutzt
// sind bisher nur VE.Bus RX/TX. GPIO 19/20 sind USB, 33-37 PSRAM, 43/44 die Konsole auf
// UART0. Die Strapping-Pins 0 und 45 bleiben frei. GPIO 3 und 46 tragen nur Signale des
// CMT2300A, die beim Start niemand treibt.
// Frei: GPIO 1, 10, 17, 18, 21, 39, 40, 47.
#pragma once

// ADuM1201 neben den S3-Pins, gewendet (Seite 1 zum S3), GPIO 4 und 5 laufen gerade hinueber:
// GPIO 4 an A0 (Ausgang des ADuM, Empfang), GPIO 5 an B1 (Eingang des ADuM, Senden).
// Seit 15.11.2026 so: TXD am RS485-Modul ist der Ausgang des Empfaengers (MS2548 Pin 1),
// siehe docs/layout_lochraster.md
#define VEBUS_RX    4
#define VEBUS_TX    5
#define VEBUS_DE    -1      // MS2548 schaltet die Richtung selbst

// Beide Zaehler am selben Pfostenstecker: GND, 3V3, Haus, WP
// So verdrahtet (14.11.2026): Haus an GPIO 7, WP an GPIO 6
#define MT681_RX    7
#define MT681_WP_RX 6       // per RMT, die UARTs sind belegt

// Kellerlueftung: zwei BME280 (0x76, 0x77) an je einem Pfostenstecker
// So verdrahtet, getestet am 14.11.2026 mit einem BME280 an 0x77
#define I2C_SDA     16
#define I2C_SCL     15

// CMT2300A (Modul 10298-V1.0) per Pigtail oben am S3 angeloetet: vier Pins nebeneinander von
// GPIO 8 bis 9, dazu VCC an 3V3 und GND. Namen wie auf dem Modul. GPIO1 bis GPIO3 des Moduls
// bleiben frei: Ohne GPIO3 fragt die Bibliothek den Paketeingang per SPI ab, GPIO2 wertet sie nicht aus.
// GPIO 46 muss beim Reset low sein, sonst gibt es keinen Download-Modus. Der interne
// Pull-down haelt ihn low, SCLK ist am CMT2300A ein Eingang.
#define CMT_CSB     8
#define CMT_SDIO    3
#define CMT_SCLK    46
#define CMT_FCSB    9

// Relais nebeneinander, Bestueckung nicht im Lochraster-Plan
#define FAN_RELAY   11
#define RELAY2      12      // Reserve

// TJA1050 unten links, ueber ADuM1201 und B0505S isoliert
// So verdrahtet (14.11.2026): RX an GPIO 13 (ADuM A0), TX an GPIO 14 (ADuM B1)
#define CAN_TX      14
#define CAN_RX      13

// JK-BMS ueber RS485, nur Zellspannungen: SC16IS752 (CJMCU-752) per SPI, Pack 1 an UART B,
// Pack 2 an UART A (kuerzere Wege im Plan), dahinter je ADuM1201, B0505S und RS485-Modul (MS2548). Die SPI-Pins liegen in denselben
// Reihen wie die Pins des Moduls, die Draehte gehen gerade hinueber. UART0 bleibt Konsole.
#define SC16_CS     2
#define SC16_MOSI   42      // SI
#define SC16_MISO   41      // SO
#define SC16_SCK    38      // SCLK
#define SC16_XTAL   1843200 // Quarz auf dem CJMCU-752, Aufdruck abgelesen am 15.11.2026

// E-Paper: Stiftleiste im Plan entfallen. Frei sind noch GPIO 1, 10, 17, 18, 21, 39, 40, 47.

// RGB-LED des Boards (WS2812), ueber die Loetbruecke "RGB" an GPIO 48
#define RGB_LED     48

// Ports am CH348: 0-5 MPPT, 6 SmartShunt, 7 frei fuer einen weiteren MPPT
